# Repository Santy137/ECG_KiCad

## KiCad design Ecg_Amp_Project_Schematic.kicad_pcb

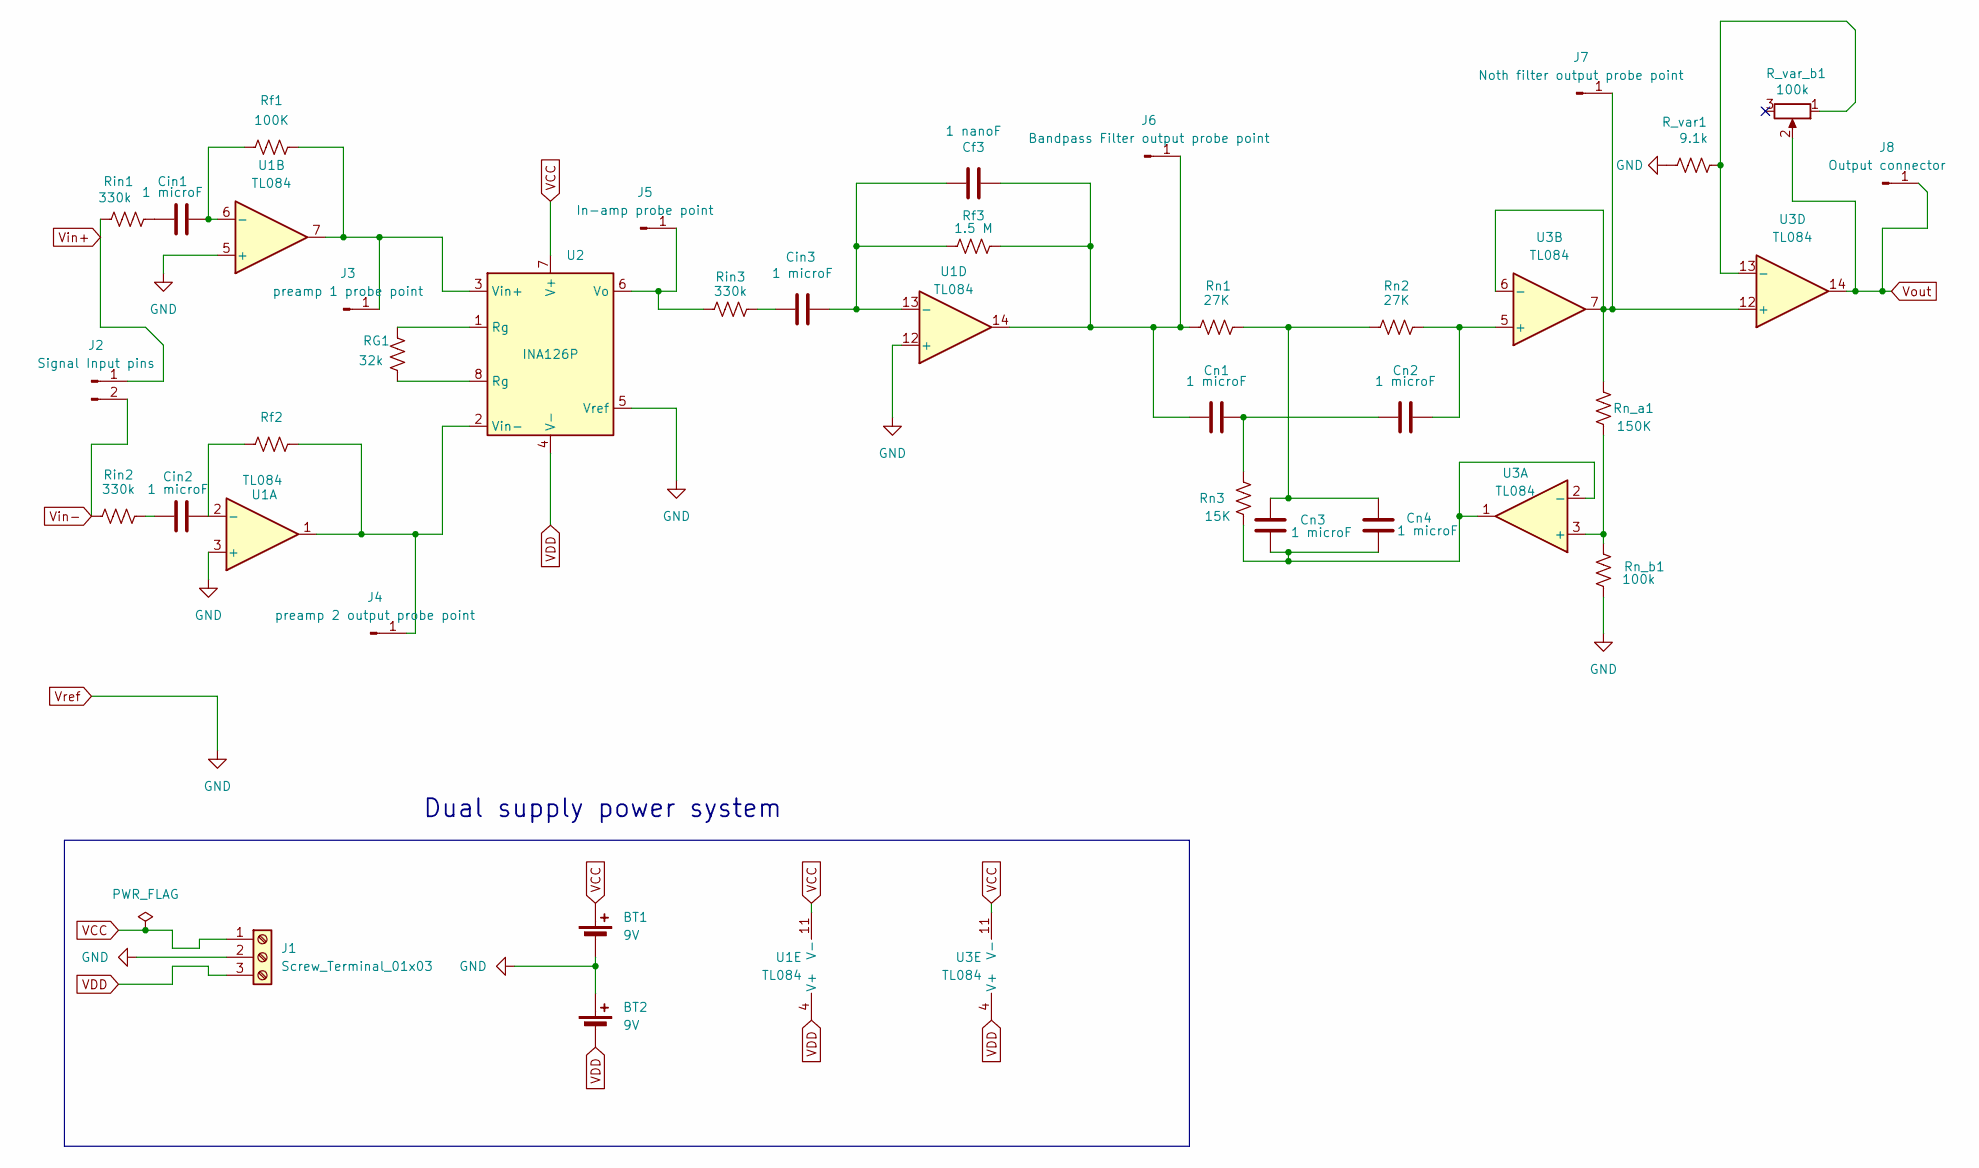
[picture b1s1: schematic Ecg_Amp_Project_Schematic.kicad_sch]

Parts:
BT1, BT2: 9V
Cf3: 1 nanoF; C_Disc_D3.0mm_W1.6mm_P2.50mm
Cin1, Cin2, Cin3: 1 microF; C_Disc_D3.0mm_W1.6mm_P2.50mm
Cn1, Cn2, Cn3, Cn4: 1 microF; C_Disc_D3.0mm_W1.6mm_P2.50mm
J1: Screw_Terminal_01x03; TerminalBlock_Phoenix_MKDS-1,5-3-5.08_1x03_P5.08mm_Horizont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
J2: Signal Input pins; PinHeader_1x02_P2.54mm_Vertical
J3: preamp 1 probe point; PinHeader_1x01_P2.54mm_Vertical
J4: preamp 2 output probe point; PinHeader_1x01_P2.54mm_Vertical
J5: In-amp probe point; PinHeader_1x01_P2.54mm_Vertical
J6: Bandpass Filter output probe point; PinHeader_1x01_P2.54mm_Vertical
J7: Noth filter output probe point; PinHeader_1x01_P2.54mm_Vertical
J8: Output connector; PinHeader_1x01_P2.54mm_Vertical
RG1: 32k; R_Axial_DIN0309_L9.0mm_D3.2mm_P12.70mm_Horizontal
R_var1: 9.1k; R_Axial_DIN0309_L9.0mm_D3.2mm_P12.70mm_Horizontal
R_var_b1: 100k; Potentiometer_Alps_RK163_Single_Horizontal
Rf1: 100K; R_Axial_DIN0309_L9.0mm_D3.2mm_P12.70mm_Horizontal
Rf2: 100k; R_Axial_DIN0309_L9.0mm_D3.2mm_P12.70mm_Horizontal
Rf3: 1.5 M; R_Axial_DIN0309_L9.0mm_D3.2mm_P12.70mm_Horizontal
Rin1, Rin2, Rin3: 330k; R_Axial_DIN0309_L9.0mm_D3.2mm_P12.70mm_Horizontal
Rn1, Rn2: 27K; R_Axial_DIN0309_L9.0mm_D3.2mm_P12.70mm_Horizontal
Rn3: 15K; R_Axial_DIN0309_L9.0mm_D3.2mm_P12.70mm_Horizontal
Rn_a1: 150K; R_Axial_DIN0309_L9.0mm_D3.2mm_P12.70mm_Horizontal
Rn_b1: 100k; R_Axial_DIN0309_L9.0mm_D3.2mm_P12.70mm_Horizontal
U1, U3: TL084; DIP-14_W7.62mm
U2: INA126P

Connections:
unnamed: Cin1.1, Rin1.2
unnamed: Cin2.1, Rin2.2
unnamed: Cin3.1, Rin3.2
unnamed: Cn1.2, Cn2.1, Rn3.1
unnamed: Cn3.1, Cn4.1, Rn1.2, Rn2.1
unnamed: J3.1 (Pin_1_1), Rf1.2, U1.7, U2.3 (Vin+)
unnamed: J4.1 (Pin_1_1), Rf2.2, U1.1, U2.2 (Vin-)
unnamed: J5.1 (Pin_1_1), Rin3.1, U2.6 (Vo)
unnamed: Cf3.2, Cn1.1, J6.1 (Pin_1_1), Rf3.2, Rn1.1, U1.14
unnamed: J7.1 (Pin_1_1), Rn_a1.1, U3.6 (-), U3.7, U3.12 (+)
unnamed: RG1.1, U2.1 (Rg)
unnamed: RG1.2, U2.8 (Rg)
unnamed: Cin2.2, Rf2.1, U1.2 (-)
unnamed: Cin1.2, Rf1.1, U1.6 (-)
unnamed: Cf3.1, Cin3.2, Rf3.1, U1.13 (-)
unnamed: Rn_a1.2, Rn_b1.1, U3.3 (+)
unnamed: Cn3.2, Cn4.2, Rn3.2, U3.1, U3.2 (-)
unnamed: Cn2.2, Rn2.2, U3.5 (+)
unnamed: R_var1.1, R_var_b1.1, U3.13 (-)
VCC: BT1.1 (+), J1.1, U1.11 (V-), U2.7 (V+), U3.11 (V-)
VDD: BT2.2 (-), J1.3, U1.4 (V+), U2.4 (V-), U3.4 (V+)
Vin+: J2.1, Rin1.1
Vin-: J2.2, Rin2.1
Vout: J8.1 (Pin_1_1), R_var_b1.2, U3.14
Vref: BT1.2 (-), BT2.1 (+), J1.2, R_var1.2, Rn_b1.2, U1.3 (+), U1.5 (+), U1.12 (+), U2.5 (Vref)

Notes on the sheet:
Dual supply power system

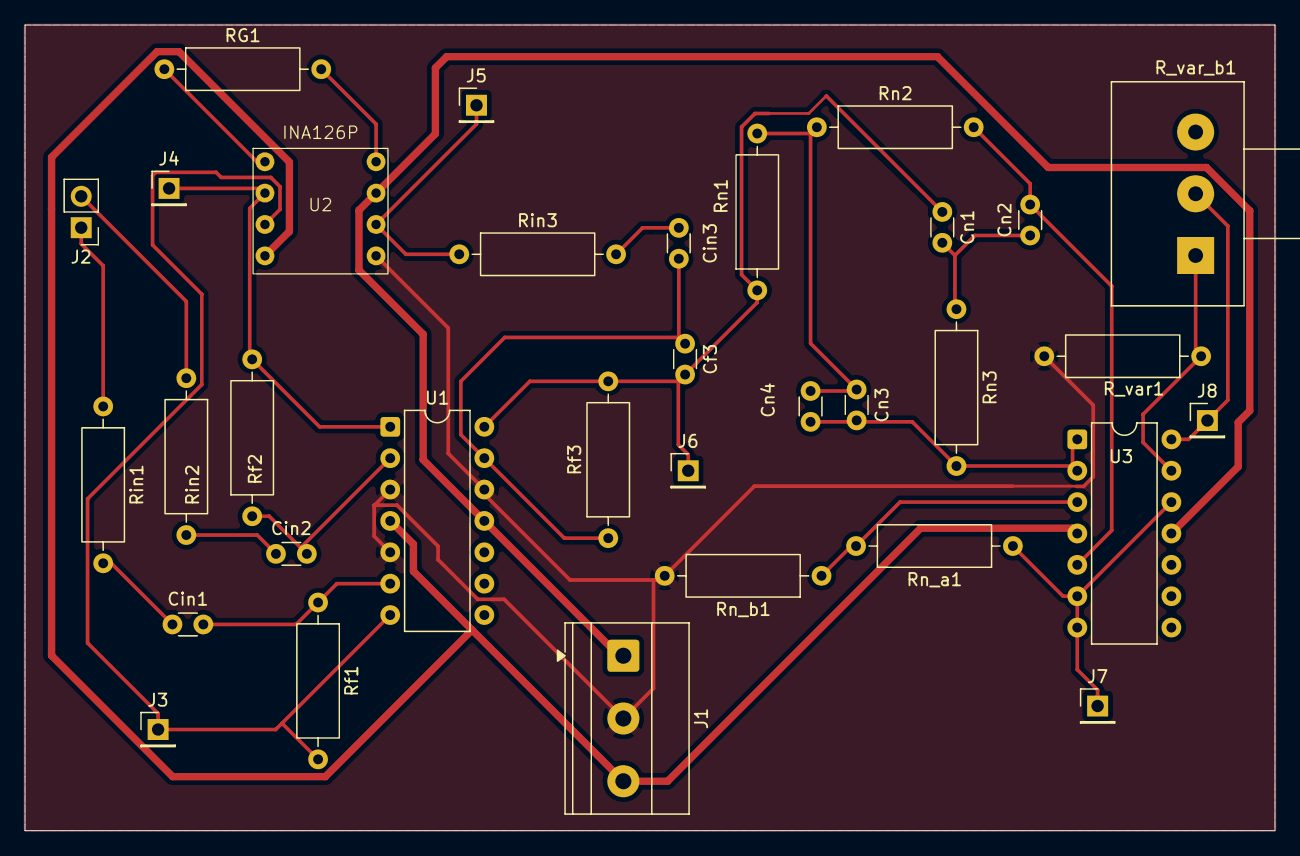
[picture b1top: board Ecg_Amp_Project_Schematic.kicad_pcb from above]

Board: 2 copper layers, 101.2 x 65.2 mm, 33 parts (0 on the bottom side), 25 nets.

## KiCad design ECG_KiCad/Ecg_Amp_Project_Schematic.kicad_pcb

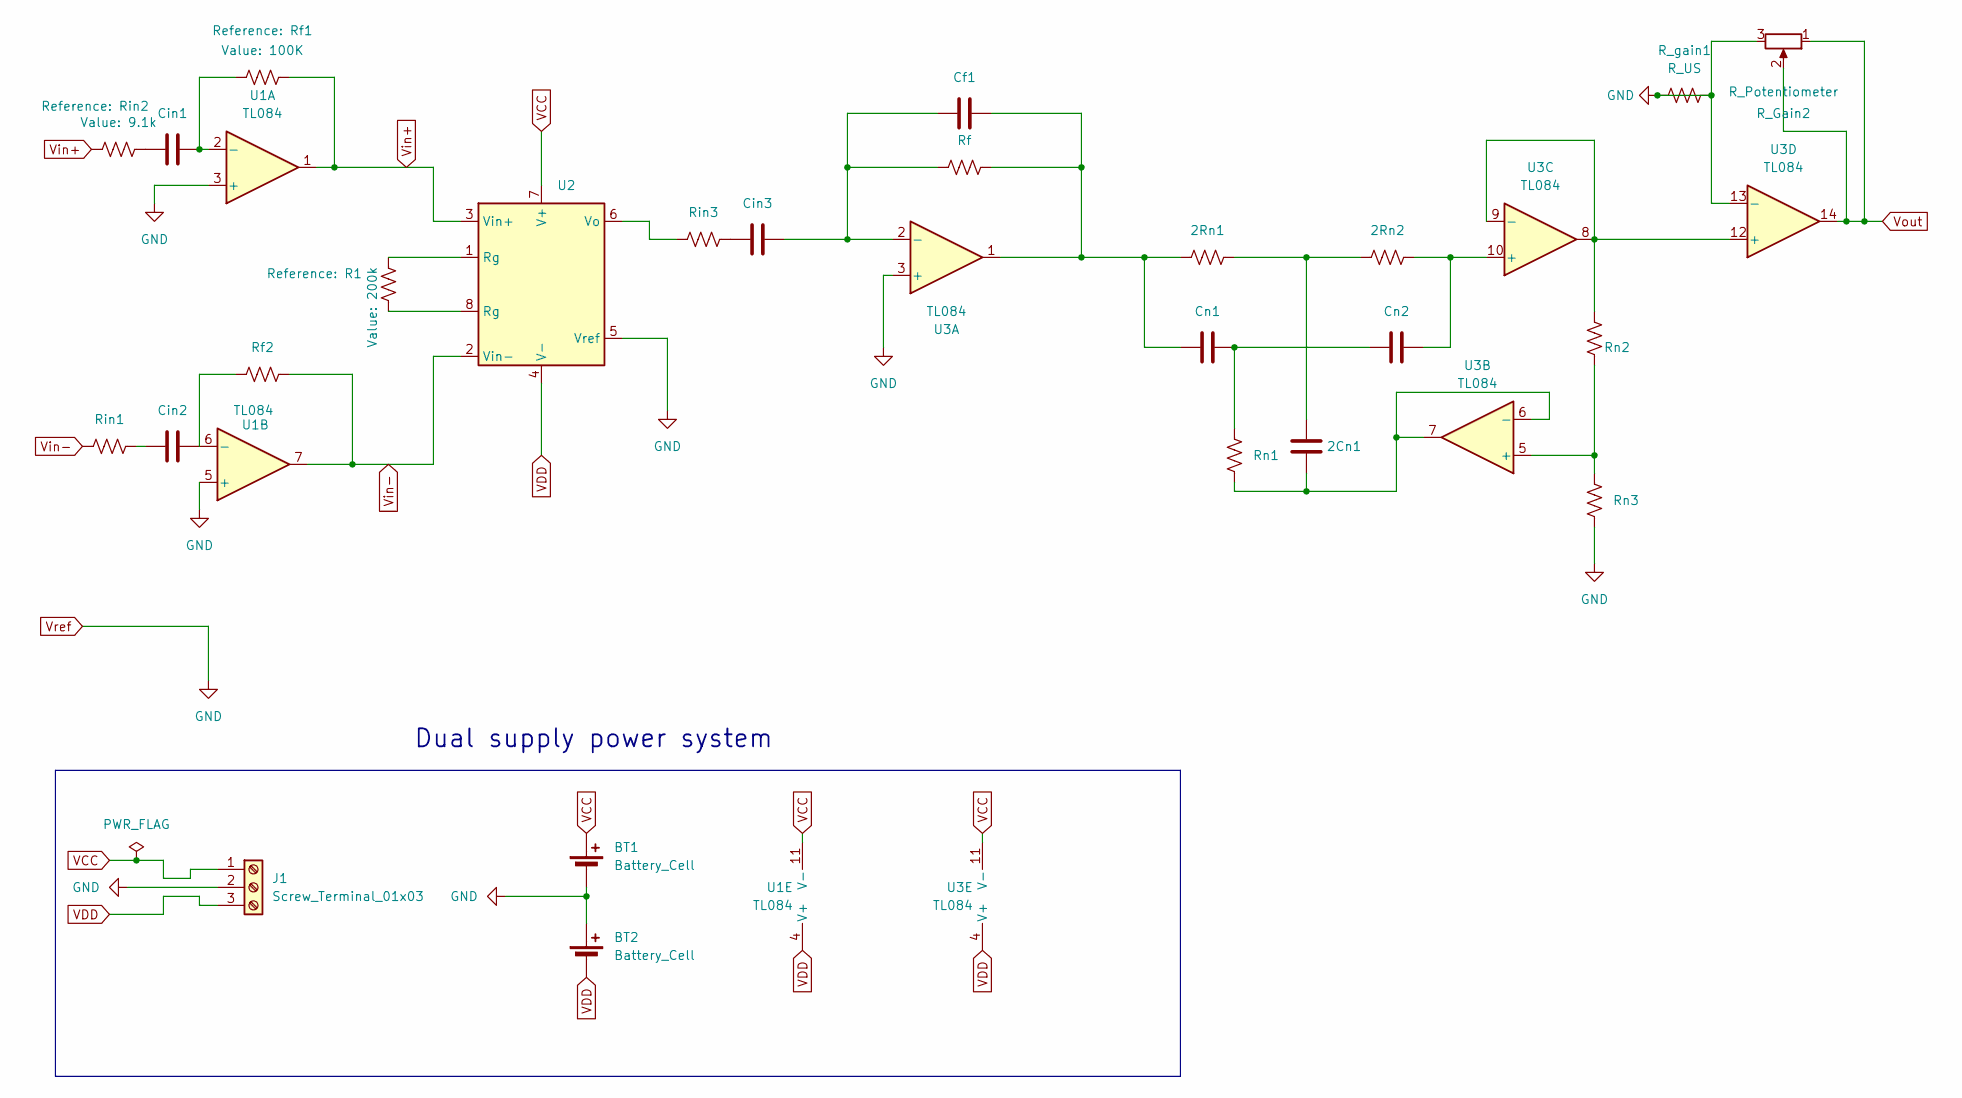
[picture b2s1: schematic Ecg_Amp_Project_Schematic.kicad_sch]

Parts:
2Cn1: C; C_Disc_D3.0mm_W1.6mm_P2.50mm
2Rn1, 2Rn2: R_US; R_Axial_DIN0309_L9.0mm_D3.2mm_P12.70mm_Horizontal
BT1, BT2: Battery_Cell
Cf1: C; C_Disc_D3.0mm_W1.6mm_P2.50mm
Cin1, Cin2, Cin3: C; C_Disc_D3.0mm_W1.6mm_P2.50mm
Cn1, Cn2: C; C_Disc_D3.0mm_W1.6mm_P2.50mm
J1: Screw_Terminal_01x03; TerminalBlock_Phoenix_MKDS-1,5-3-5.08_1x03_P5.08mm_Horizont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
R1: 200k; R_Axial_DIN0309_L9.0mm_D3.2mm_P12.70mm_Horizontal
R2: Rf; R_Axial_DIN0309_L9.0mm_D3.2mm_P12.70mm_Horizontal
R_Gain2: R_Potentiometer; Potentiometer_Alps_RK163_Single_Horizontal
R_gain1: R_US; R_Axial_DIN0309_L9.0mm_D3.2mm_P12.70mm_Horizontal
Rf1: 100K; R_Axial_DIN0309_L9.0mm_D3.2mm_P12.70mm_Horizontal
Rf2: R_US; R_Axial_DIN0309_L9.0mm_D3.2mm_P12.70mm_Horizontal
Rin1, Rin3: R_US; R_Axial_DIN0309_L9.0mm_D3.2mm_P12.70mm_Horizontal
Rin2: 9.1k; R_Axial_DIN0309_L9.0mm_D3.2mm_P12.70mm_Horizontal
Rn1, Rn2, Rn3: R_US; R_Axial_DIN0309_L9.0mm_D3.2mm_P12.70mm_Horizontal
U1, U3: TL084; DIP-14_W7.62mm
U2: INA126P

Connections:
unnamed: 2Cn1.1, 2Rn1.2, 2Rn2.1
unnamed: 2Rn1.1, Cf1.2, Cn1.1, R2.2, U3.1
unnamed: Cin1.1, Rin2.2
unnamed: Cin2.1, Rin1.2
unnamed: Cin3.1, Rin3.2
unnamed: Cn1.2, Cn2.1, Rn1.1
unnamed: R1.1, U2.1 (Rg)
unnamed: R1.2, U2.8 (Rg)
unnamed: Cin1.2, Rf1.1, U1.2 (-)
unnamed: Cin2.2, Rf2.1, U1.6 (-)
unnamed: Rin3.1, U2.6 (Vo)
unnamed: Cf1.1, Cin3.2, R2.1, U3.2 (-)
unnamed: Rn2.2, Rn3.1, U3.5 (+)
unnamed: 2Cn1.2, Rn1.2, U3.6 (-), U3.7
unnamed: 2Rn2.2, Cn2.2, U3.10 (+)
unnamed: Rn2.1, U3.8, U3.9 (-), U3.12 (+)
VCC: BT1.1 (+), J1.1, U1.11 (V-), U2.7 (V+), U3.11 (V-)
VDD: BT2.2 (-), J1.3, U1.4 (V+), U2.4 (V-), U3.4 (V+)
Vin+: Rf1.2, Rin2.1, U1.1, U2.3 (Vin+)
Vin-: Rf2.2, Rin1.1, U1.7, U2.2 (Vin-)
Vout: R_Gain2.1, R_Gain2.2, U3.14
Vref: BT1.2 (-), BT2.1 (+), J1.2, R_Gain2.3, R_gain1.1, R_gain1.2, Rn3.2, U1.3 (+), U1.5 (+), U2.5 (Vref), U3.3 (+), U3.13 (-)

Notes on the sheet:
Dual supply power system

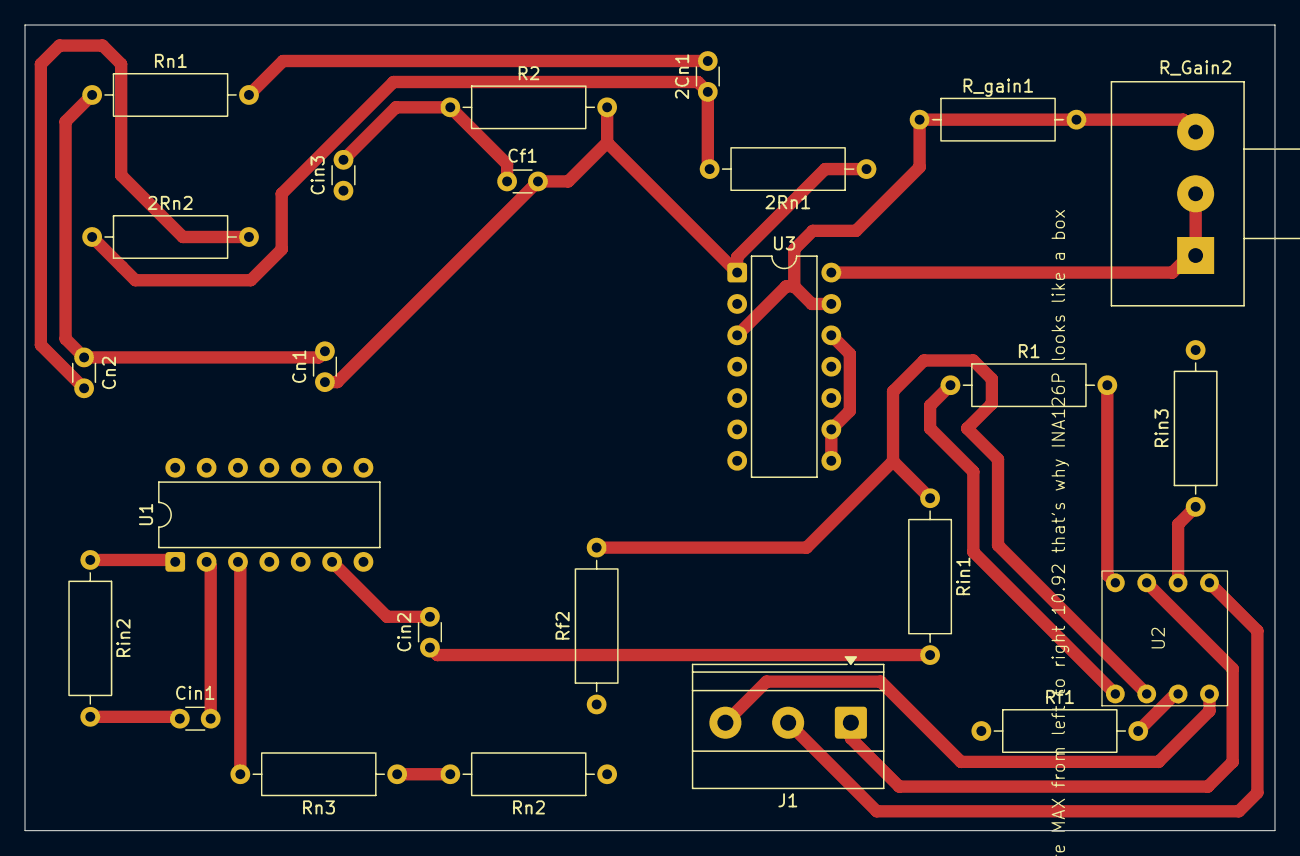
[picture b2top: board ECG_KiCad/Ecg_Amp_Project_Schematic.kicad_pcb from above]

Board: 2 copper layers, 101.2 x 65.2 mm, 25 parts (0 on the bottom side), 22 nets.
